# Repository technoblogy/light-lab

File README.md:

# Light Lab
Experiment with different patterns on RGB LED NeoPixel (WS2812 or WS2812B) or DotStar (APA102 or SK9822) strips.

For more information see <http://www.technoblogy.com/show?5DCO>.

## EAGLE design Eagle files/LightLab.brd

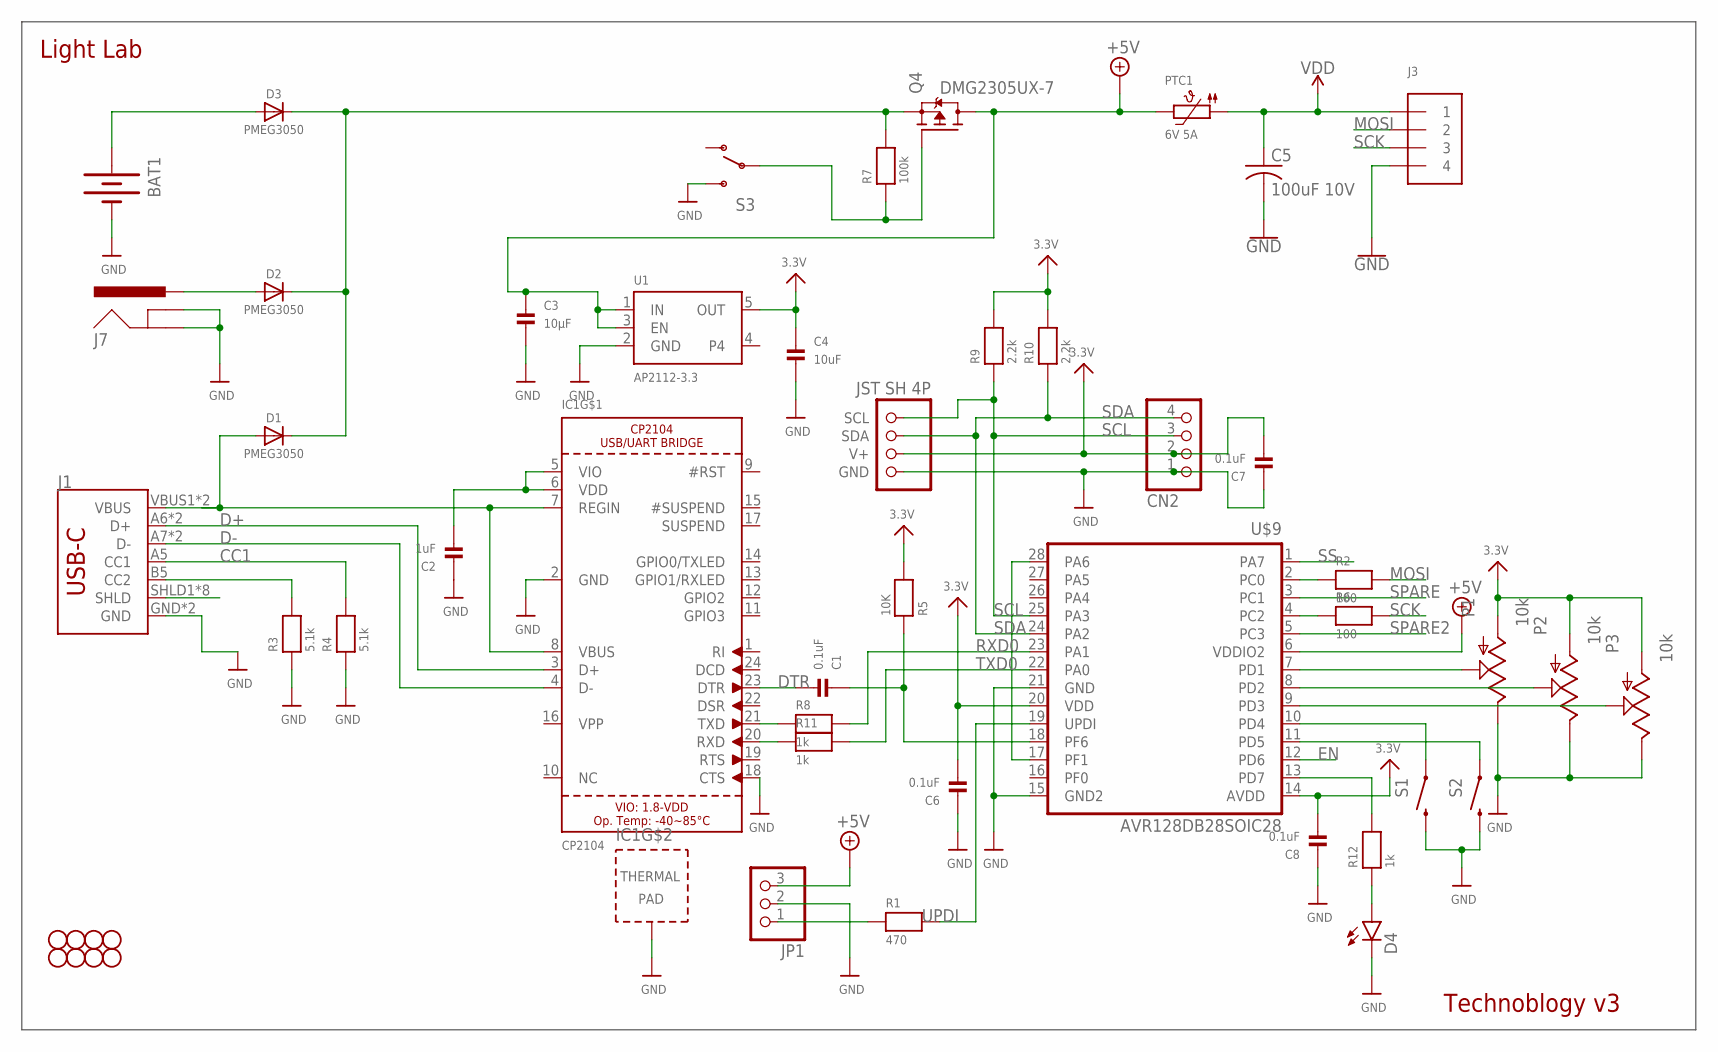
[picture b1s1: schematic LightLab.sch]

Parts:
BAT1: BATTERY18650; BATTERY_18650-HOLDER
C1, C6, C7, C8: 0.1uF; _0805MP
C2: 1uF; _0805MP
C3: 10µF; _0805MP
C4: 10uF; _0805MP
C5: 100uF 10V; C1210
CN2: HEADER-1X4ROUND; 1X04_ROUND
CONN1: JST SH 4P; JST_SH4
D1, D2, D3: PMEG3050; SOD-128
D4: LED1206-BOTTOM; LED-1206-BOTTOM
IC1: CP2104; QFN24_4MM_SMSC
J1: USB_C2-LAYER; USB-C-16P
J3: TERMBLOCK_1X4; TERMBLOCK_1X3-3.5MM
J7: 5.5x2.1mm Barrel; POWER_JACK_SMD
JP1: HEADER-1X3ROUND; 1X03_ROUND
JP8, JP9, JP10, JP11, JP12, JP13, JP14, JP15: STAND-OFF
P1, P2, P3: 10k; ALPS_POT
PTC1: 6V 5A; PTC1210
Q4: DMG2305UX-7; SOT23-WIDE
R1: 470; _0805MP
R2, R6: 100; _0805MP
R3, R4: 5.1k; _0805MP
R5: 10K; _0805MP
R7: 100k; _0805MP
R8, R11, R12: 1k; _0805MP
R9, R10: 2.2k; _0805MP
S1, S2: SWITCH-MOMENTARY-2PTH; TACTILE-PTH
S3: SWITCH-SPDTKIT; SWITCH-SPDT_KIT
U1: AP2112-3.3; SOT23-5
U$9: AVR128DB28SOIC28; SO-28W

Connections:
3.3V: C4.1, C6.2, C7.2, C8.2, CN2.2, CONN1.2 (V+), P1.P$3 (A), P2.P$3 (A), P3.P$3 (A), R5.2, R9.2, R10.2, U1.5 (OUT), U$9.14 (AVDD), U$9.20 (VDD)
+5V: C3.1, JP1.3, PTC1.P$2 (2), Q4.3 (D), U1.1 (IN), U1.3 (EN), U$9.6 (VDDIO2)
BAT+: BAT1.PWR@1 (+), D3.A
CC1: J1.A5 (CC1), R4.2
CC2: J1.B5 (CC2), R3.2
D+: IC1.3 (D+), J1.A6 (D+), J1.B6 (D+)
D-: IC1.4 (D-), J1.A7 (D-), J1.B7 (D-)
DTR: C1.2, IC1.23 (DTR)
EN: U$9.12 (PD6)
GND: BAT1.GND@1 (-), C2.1, C3.2, C4.2, C5.2, C6.1, C7.1, C8.1, CN2.1, CONN1.1 (GND), D4.C, IC1.2 (GND), IC1.18 (CTS), IC1.THERM (TP), J1.GND, J1.GND2 (GND), J3.4, J7.GND (GNDBREAK), J7.P$4 (GND), JP1.2, P1.P$1 (E), P2.P$1 (E), P3.P$1 (E), R3.1, R4.1, S1.3 (2), S2.3 (2), S3.3 (S), U1.2 (GND), U$9.15 (GND2), U$9.21 (GND)
MOSI: J3.2, R2.2
unnamed: P1.P$2 (S), U$9.7 (PD1)
unnamed: D4.A, R12.1
unnamed: R12.2, U$9.13 (PD7)
unnamed: IC1.20 (RXD), R11.1
unnamed: Q4.1 (G), R7.1, S3.2
unnamed: P2.P$2 (S), U$9.8 (PD2)
unnamed: C2.2, IC1.5 (VIO), IC1.6 (VDD)
unnamed: S1.1, U$9.10 (PD4)
unnamed: R2.1, U$9.2 (PC0)
unnamed: P3.P$2 (S), U$9.9 (PD3)
unnamed: S2.1, U$9.11 (PD5)
unnamed: U$9.17 (PF1), U$9.28 (PA6)
unnamed: R6.1, U$9.4 (PC2)
unnamed: D1.C, D2.C, D3.C, Q4.2 (S), R7.2
unnamed: IC1.21 (TXD), R8.1
unnamed: JP1.1, R1.1
unnamed: D2.A, J7.VIN0 (PWR)
RESET: C1.1, R5.1, U$9.18 (PF6)
RXD0: R8.2, U$9.23 (PA1)
SCK: J3.3, R6.2
SCL: CN2.3, CONN1.4 (SCL), R9.1, U$9.25 (PA3)
SDA: CN2.4, CONN1.3 (SDA), R10.1, U$9.24 (PA2)
SHIELD: J1.SHLD1 (SHLD), J1.SHLD2 (SHLD), J1.SHLD3 (SHLD), J1.SHLD4 (SHLD), J1.SHLD5 (SHLD), J1.SHLD6 (SHLD), J1.SHLD7 (SHLD), J1.SHLD8 (SHLD)
SPARE: U$9.3 (PC1)
SPARE2: U$9.5 (PC3)
SS: U$9.1 (PA7)
TXD0: R11.2, U$9.22 (PA0)
UPDI: R1.2, U$9.19 (UPDI)
VBUS: D1.A, IC1.7 (REGIN), IC1.8 (VBUS), J1.VBUS1 (VBUS), J1.VBUS2 (VBUS)
VDD: C5.1, J3.1, PTC1.P$1 (1)

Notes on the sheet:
Light Lab
Technoblogy v3

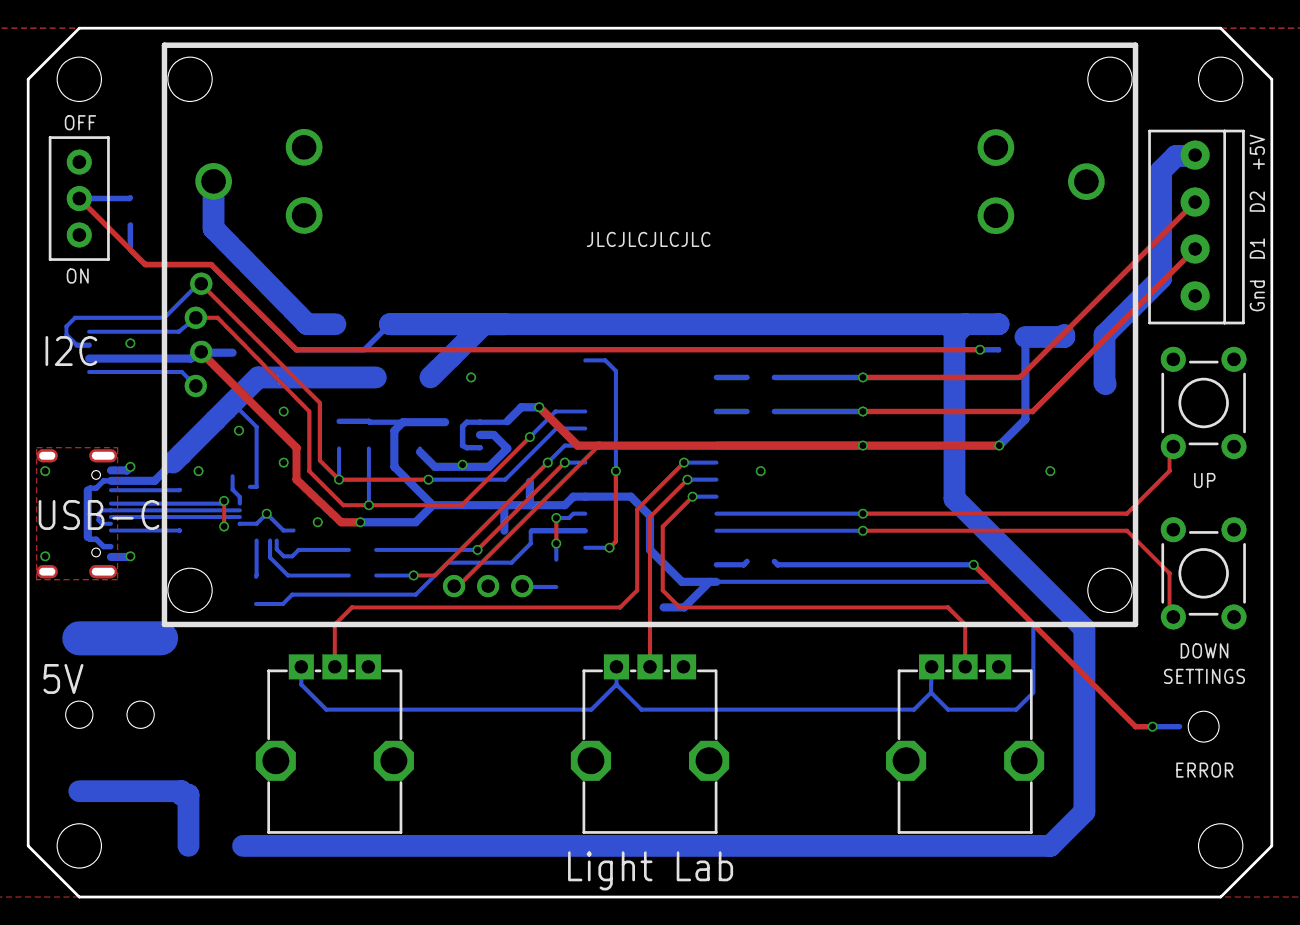
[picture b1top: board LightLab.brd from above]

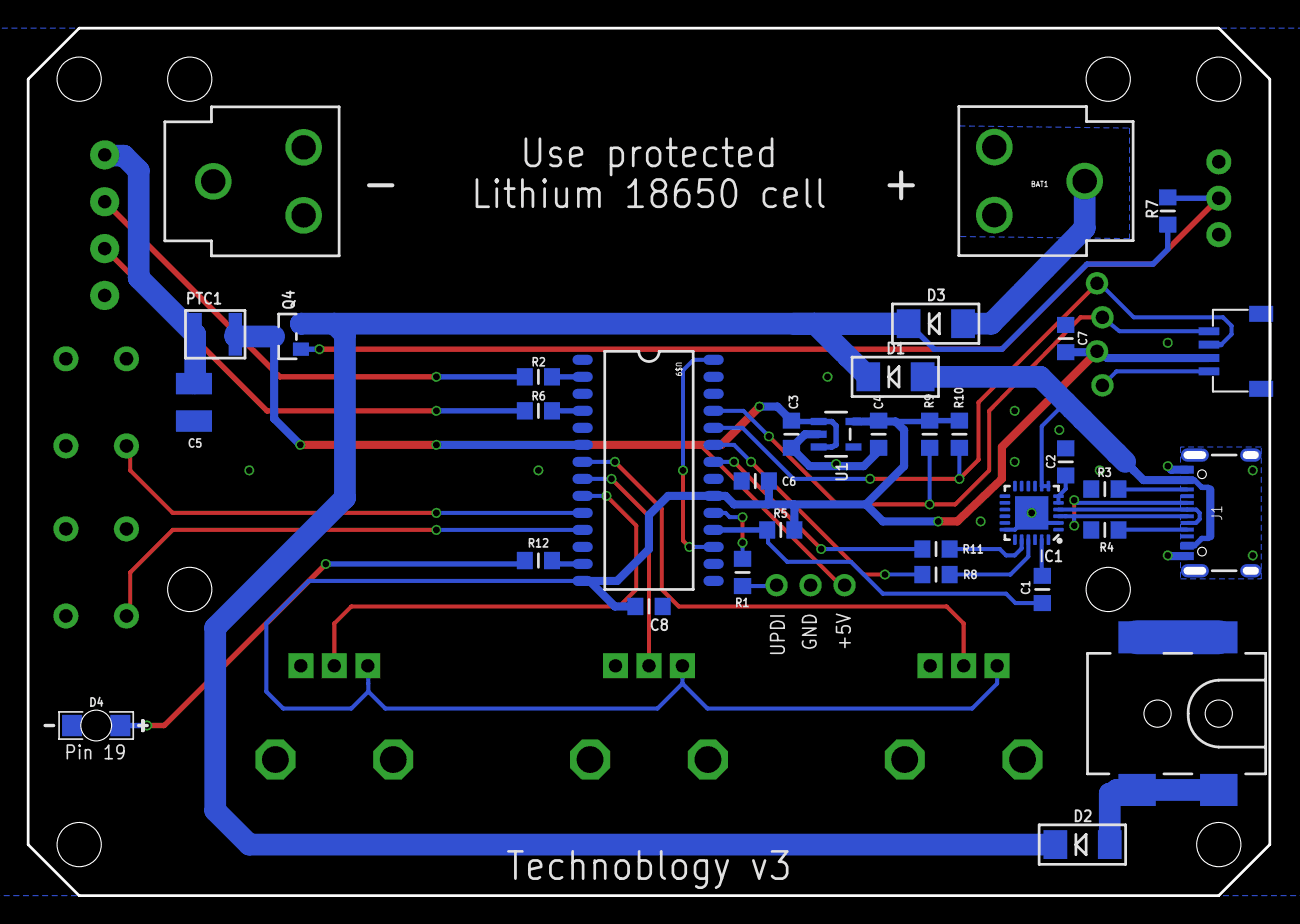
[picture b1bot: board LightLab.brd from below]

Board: 2 copper layers, 92.3 x 64.4 mm, 50 parts (33 on the bottom side), 37 nets.

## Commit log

2026-01-14 Version 1 - 14th January 2026

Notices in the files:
parts and their libraries:
SparkFun-Connectors: Licensing: Creative Commons ShareAlike 4.0 International - https://creativecommons.org/licenses/by-sa/4.0
microbuilder: This work is placed in the public domain, and may be freely used for commercial and non-commercial work with the following conditions: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
